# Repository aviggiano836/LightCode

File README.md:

LightCode
=========

_Lighting the way to teach programming_

## About project
* [LightCode Website](https://aviggiano836.github.io/LightCode/)
* [WiCHacks 2017](http://wichacks.rit.edu/) project submission
* [DevPost project page](https://devpost.com/software/light-code)
* [See a demo](https://youtu.be/sbjNLAihfJ0)

## What is it?

We wanted to do something involving hardware and make something that would encourage people to learn how to code.

The end product for users is a battery-powered desk light with individually addressable RGB LEDs and sensors that the user learns to code to produce light matters based on the sensor's inputs. The users mix and match these lights for a string of colorful lights. The lights are covered in clear shapes (our prototypes are paper flowers).

## How we built it

For the programming side, we developed a simple [Scratch](https://scratch.mit.edu/)-like program for the users to code in to introduce them to coding in the [Arduino](https://www.arduino.cc/) language. This block code will be translated into the Arduino language and sent to the Arduino connected to the computer.

For the hardware/electronics, we prototyped our modular product using a 4-stranded cable and lots of header pins. We used an Arduino Uno to handle the software, making quick temporary electronic circuits using a breadboard and jumper wires. We used several RGB LEDs controlled by ws2811 driver chips and a photo-resistor that changes resistance when exposed to light.

## What's next

* Integrate with MIT Scratch or related Open Source projects such as Snap4Arduino
* Order custom PCBs and 3D print to work towards a more polished final product
* Create an online presence with lots of tutorial type things

## License

GPLv3

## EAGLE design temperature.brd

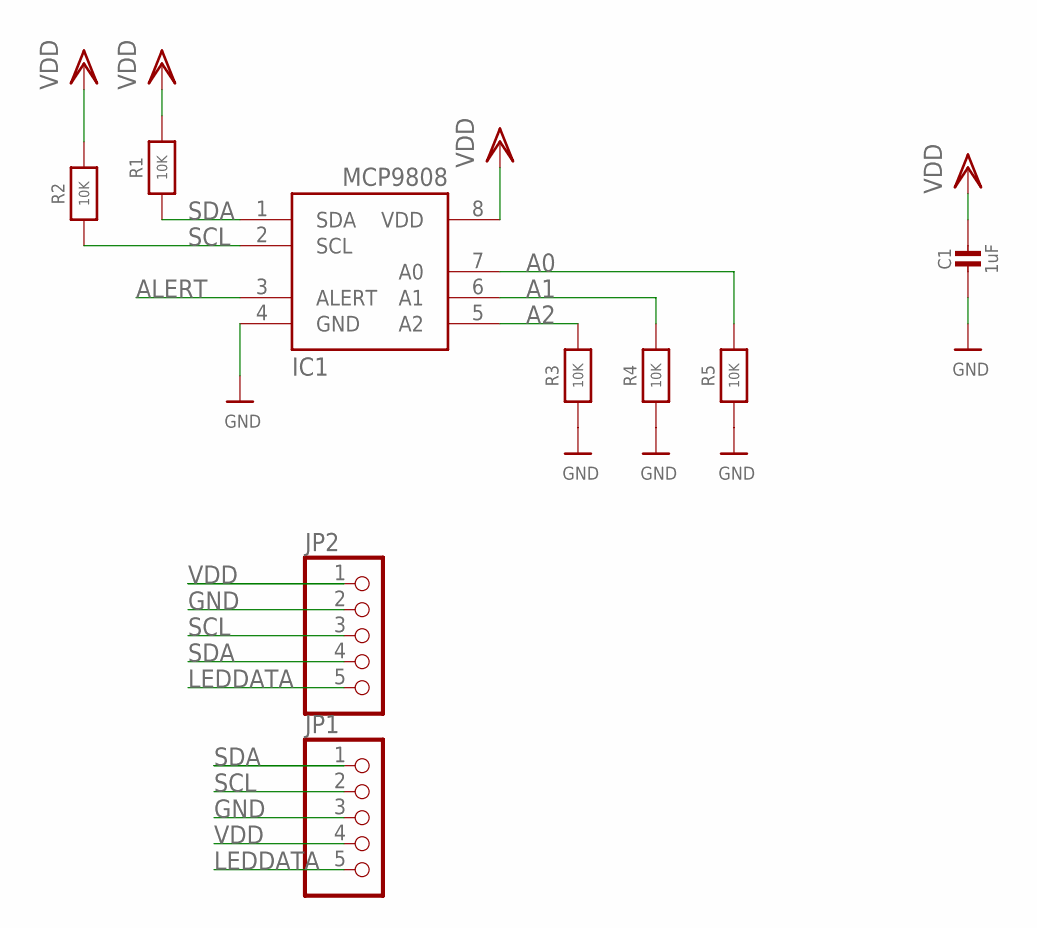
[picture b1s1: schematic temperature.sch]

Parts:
C1: 1uF; _0805MP
IC1: MCP9808-E/MS; MSOP8_0.65MM
JP1, JP2: PINHD-1X55X2MM; 1_05X2MM
R1, R2, R3, R4, R5: 10K; 0805-NO

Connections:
A0: IC1.7 (A0), R5.2
A1: IC1.6 (A1), R4.2
A2: IC1.5 (A2), R3.2
ALERT: IC1.3 (ALERT)
GND: C1.2, IC1.4 (GND), JP1.3, JP2.2, R3.1, R4.1, R5.1
LEDDATA: JP1.5, JP2.5
SCL: IC1.2 (SCL), JP1.2, JP2.3, R2.1
SDA: IC1.1 (SDA), JP1.1, JP2.4, R1.1
VDD: C1.1, IC1.8 (VDD), JP1.4, JP2.1, R1.2, R2.2

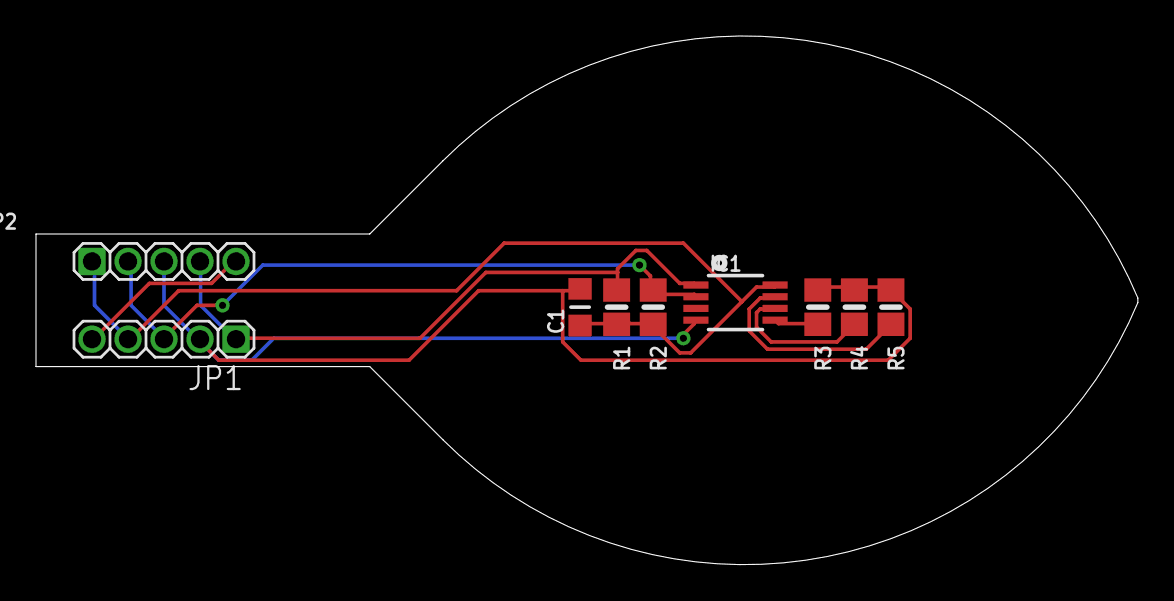
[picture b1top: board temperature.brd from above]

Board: 2 copper layers, 61.2 x 29.4 mm, 9 parts (0 on the bottom side), 8 nets.

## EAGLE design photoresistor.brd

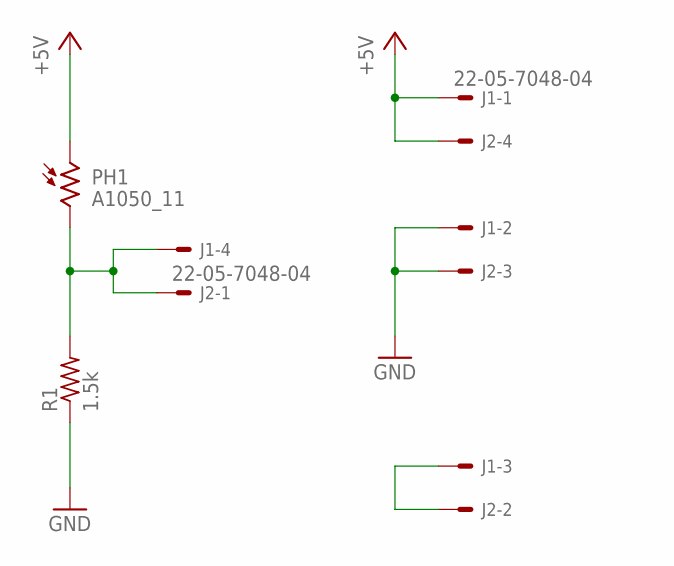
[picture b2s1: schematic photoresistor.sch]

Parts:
J1, J2: 22-05-7048-04; 7395-04
PH1: A1050_11; T0-46-A10XX
R1: 1.5k; M0805

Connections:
+5V: J1.1, J2.4, PH1.1
GND: J1.2, J2.3, R1.1
unnamed: J1.3, J2.2
unnamed: J1.4, J2.1, PH1.2, R1.2

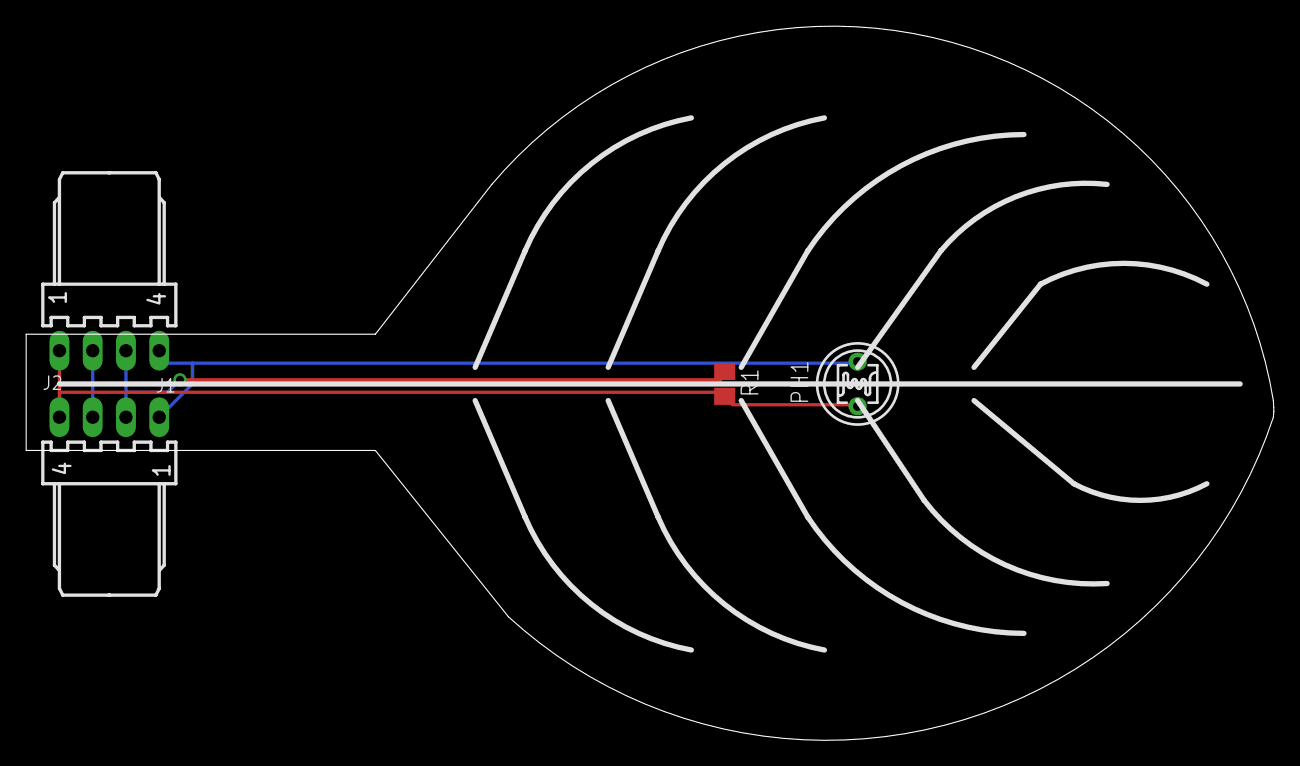
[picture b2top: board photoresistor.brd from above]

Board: 2 copper layers, 95.3 x 54.5 mm, 4 parts (0 on the bottom side), 4 nets.

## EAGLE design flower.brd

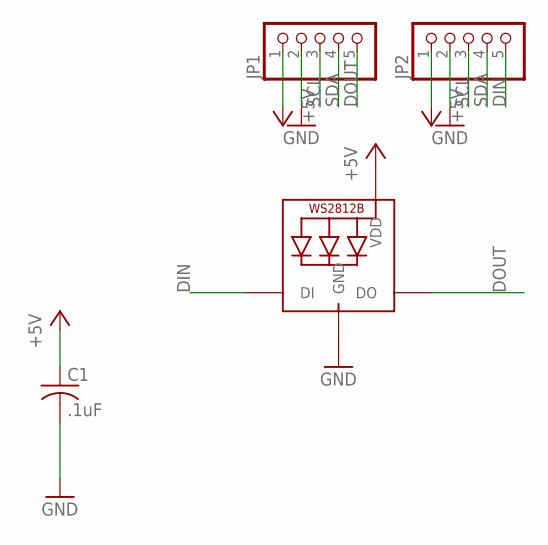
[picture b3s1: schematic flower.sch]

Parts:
C1: .1uF; C0805
JP1, JP2: PINHD-1X55X2MM; 1_05X2MM
LED1: WS2812B_5050N; WS2812B-NARROW

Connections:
+5V: C1.1, JP1.1, JP2.1, LED1.1-VDD (VDD)
DIN: JP2.5, LED1.4-DIN (DI)
DOUT: JP1.5, LED1.2-DOUT (DO)
GND: C1.2, JP1.2, JP2.2, LED1.3-GND (GND)
SCL: JP1.3, JP2.3
SDA: JP1.4, JP2.4

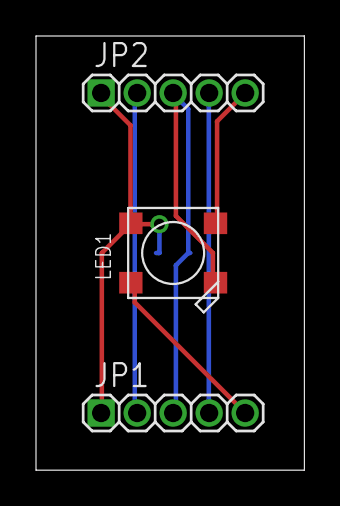
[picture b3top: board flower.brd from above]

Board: 2 copper layers, 14.9 x 24.1 mm, 4 parts (1 on the bottom side), 6 nets.

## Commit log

2017-02-26 Add a README explaining the project (based on DevPost entry)
2017-02-26 Add license file. Close #6. Thanks!
2017-02-26 add license to readme
2017-02-26 changed all blocks to commands needed for the arduino and neopixels '
2017-02-26 add gh pages files
2017-02-26 add github pages site to readme
2017-02-26 starting writing code to file when saved
2017-02-26 add more content
2017-02-26 asdf
2017-03-09 added more commands, set up file saving and started translation to arduino language
2017-03-09 fixed complier and started breaking down methods to make it more reusable
2017-03-10 broke up code writing for reusability and easy reading
2017-03-11 set up upload functions, managed to open up command prompt to the arduino file to run ardiuno commands
2017-05-06 Added Clear flower changed show for to delay for fixed set flower to use the color picked
2017-05-06 Fixed loops, while, and if to contain interior blocks correctly

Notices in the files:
parts and their libraries:
microbuilder: This work is placed in the public domain, and may be freely used for commercial and non-commercial work with the following conditions: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
